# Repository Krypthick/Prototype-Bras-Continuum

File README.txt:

Base:

base_housing:
Le boîtier principal agit comme une base pour le bras. Il utilise des inserts chauffants filetés et des boulons M3.
Il contient :
	-circuit principal
	-circuit des pilotes pas à pas
	-circuit du système de gestion de batterie
	-les batteries
	-interrupteur
	-prise cylindrique DC

==============================
base_battery_retainer:
La pièce qui maintient les batteries en place.

==============================
base_motion_motor_housing:
Couvercle qui s'attache au boîtier avec des boulons M3 et tient les moteurs pas à pas.

==============================
base_fixed_segment:
Premier segment.

==============================
base_spacer_fixed_segment:
Espaceur entre (base_fixed_segment) et (base_motion_motor_housing), fixé avec des boulons M5. Fournit l'espace nécessaire pour les poulies attachées au réducteur.

============================================================
Gearbox:

gearbox_motor_gear:
Engrenage attaché et entraîné par le moteur pas à pas. Engrenage soleil.

==============================
gearbox_planet_gear:
Engrenage planète, aussi appelé satellite. Il y en a trois pour avoir un réducteur stable.

==============================
gearbox_ring_gear:
L'engrenage fixé au moteur pas à pas avec des boulons M3 a aussi comme fonction de contenir les pièces du réducteur.

==============================
gearbox_orbit:
La pièce qui relie les trois engrenages planètes et est attachée à l'arbre avec des boulons et écrous M4.

==============================
gearbox_shaft:
L'arbre attaché aux engrenages planètes et auquel on attache la poulie.

==============================
gearbox_shaft_attachment:
La poulie qui tient la corde permettant le mouvement du bras.

======================================================
Hand:

hand_segment:
Le dernier segment qui tient le support de la main avec des boulons et écrous M5 et tient la fin de la corde.

==============================

hand_motor_finger_mount:
Le support qui tient le petit moteur pas à pas avec des boulons M3 ainsi que les deux doigts de la pince avec des boulons M5.

==============================

hand_gripper:
Le doigt de la pince qui contient un roulement à billes 606z.

==============================

hand_bearing_M5_spacer:
La pièce qui relie le boulon M5 de diamètre 5 mm et le roulement à billes ayant un diamètre intérieur de 6 mm.

======================================================
Manette:

manette_housing:
Boîtier de la manette qui contient le circuit de la manette, la batterie 9V et le joystick. Il utilise des inserts chauffants filetés et des boulons M3.

==============================
manette_lid:
Le couvercle du boîtier de la manette attaché avec des boulons M3.

==============================
manette_pin:
La pièce qui permet d'utiliser les boutons de la manette plus facilement depuis l'extérieur.

======================================================
Segment:

La pièce principale qui guide la corde et donne la flexibilité nécessaire pour le mouvement du bras. Chaque segment a un boulon et un écrou M4, mais aussi une boule filetée de 10 mm de diamètre qui permet la rotation entre les différents segments.

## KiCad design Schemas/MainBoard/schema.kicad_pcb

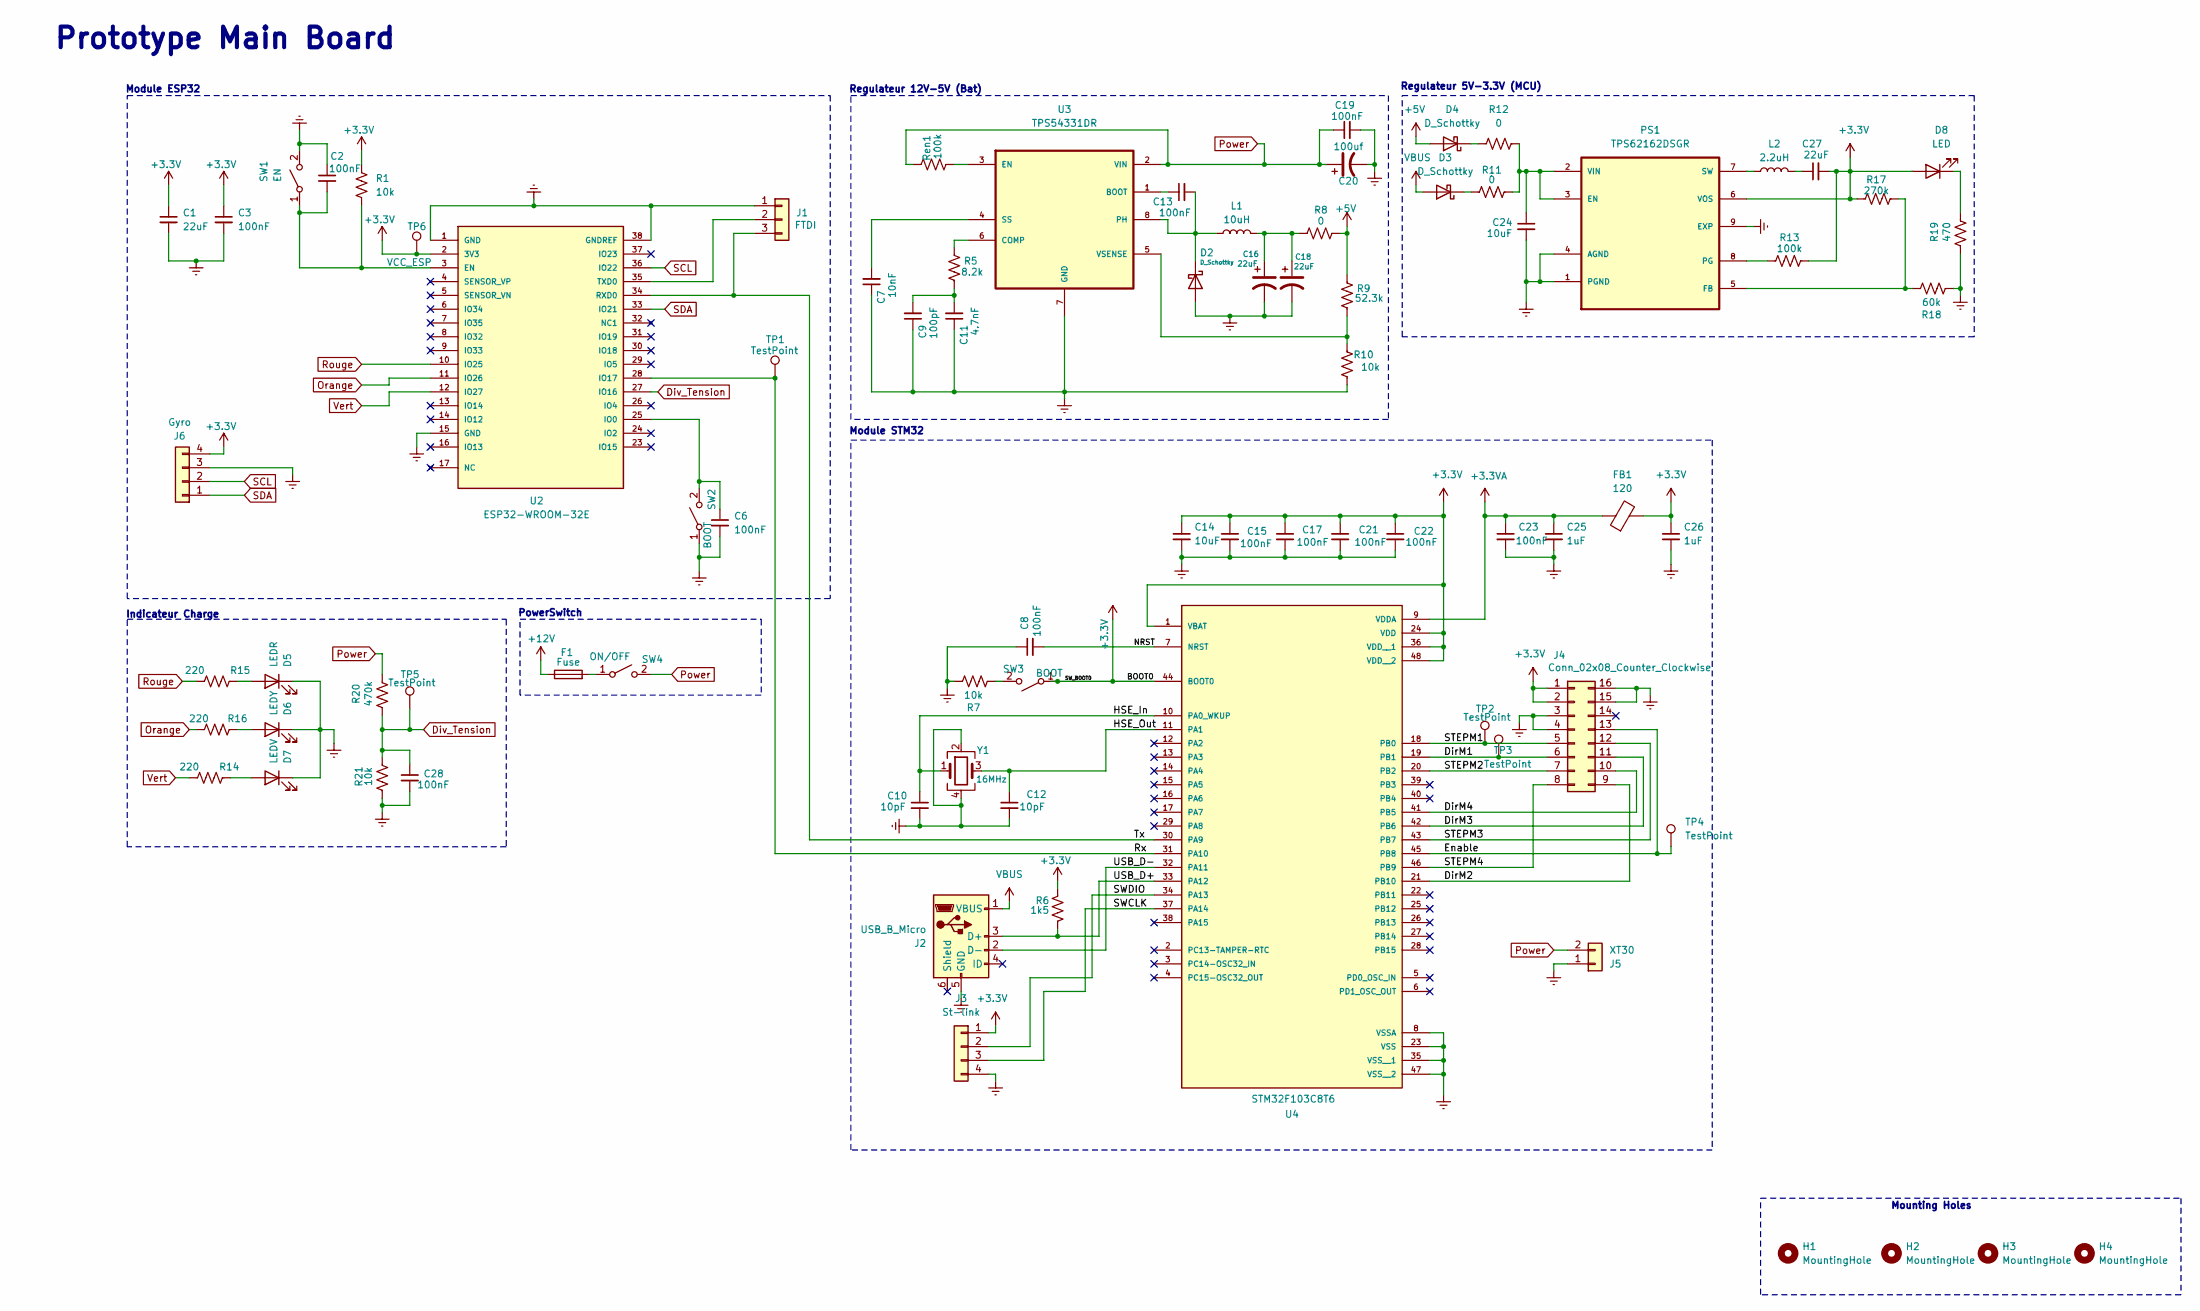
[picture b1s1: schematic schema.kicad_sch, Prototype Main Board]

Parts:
C1, C16, C18, C27: 22uF; C_0805_2012Metric_Pad1.18x1.45mm_HandSolder; MPN CL10A226MP8NUNE
C2, C3, C6, C8, C13, C15, C17, C19, C21, C22, C23: 100nF; C_0603_1608Metric_Pad1.08x0.95mm_HandSolder; MPN C0603C104K5RACTU
C7: 10nF; C_0603_1608Metric_Pad1.08x0.95mm_HandSolder; MPN CL10B103KB8NNNC
C9: 100pF; C_0603_1608Metric_Pad1.08x0.95mm_HandSolder; MPN CL10C101JB8NNNC
C10, C12: 10pF; C_0603_1608Metric_Pad1.08x0.95mm_HandSolder; MPN C0603C100J5GACTU
C11: 4.7nF; C_0603_1608Metric_Pad1.08x0.95mm_HandSolder; MPN CL10B473KB8NNNC
C14, C24: 10uF; C_0805_2012Metric_Pad1.18x1.45mm_HandSolder; MPN CL21B106KOQNNNE
C20: 100uf; CAP_YX_6P3X11_RUB; MPN 35ZLH100MEFC6.3X11
C25, C26: 1uF; C_0603_1608Metric_Pad1.08x0.95mm_HandSolder; MPN CL10B105KP8NNNC
C28: 100nF; C_0805_2012Metric_Pad1.18x1.45mm_HandSolder; MPN C0805C104K5RACTU
D2, D3, D4: D_Schottky; CDBC-G; MPN CDBC560-G
D5: LEDR; LED_0805_2012Metric_Pad1.15x1.40mm_HandSolder; MPN LTST-C171KRKT
D6: LEDY; LED_0805_2012Metric_Pad1.15x1.40mm_HandSolder; MPN LTST-C171KSKT
D7: LEDV; LED_0805_2012Metric_Pad1.15x1.40mm_HandSolder; MPN LTST-C171KGKT
D8: LED; LED_0805_2012Metric_Pad1.15x1.40mm_HandSolder; MPN LTST-C171KGKT
F1: Fuse; FUSC6125X279N; MPN 0679H9100-05
FB1: 120; L_0603_1608Metric_Pad1.05x0.95mm_HandSolder; MPN MI0603M121R-10
H1, H2, H3, H4: MountingHole; MountingHole_3.2mm_M3_DIN965_Pad
J1: FTDI; PinHeader_1x03_P2.54mm_Vertical
J2: USB_B_Micro; AMPHENOL_10118192-0001LF; MPN 10118192-0001LF
J3: St-link; PinHeader_1x04_P2.54mm_Vertical; MPN 61300411121
J4: Conn_02x08_Counter_Clockwise; CONN_7024616xx_MOL; MPN 0702461601
J5: XT30; AMASS_XT30U-M_1x02_P5.0mm_Vertical; MPN FIT0586
J6: Gyro; PinHeader_1x04_P2.54mm_Vertical; MPN 61300411121
L1: 10uH; IND_IHLP-4040DZ_VIS; MPN IHLP4040DZER100M01
L2: 2.2uH; INDC3225X170N; MPN BRL3225T2R2M
PS1: TPS62162DSGR; SON50P200X200X80-9N; PARTREV E
R1, R7, R10: 10k; R_0603_1608Metric_Pad0.98x0.95mm_HandSolder; MPN RC0603FR-0710KL
R5: 8.2k; R_0603_1608Metric_Pad0.98x0.95mm_HandSolder; MPN ERJ-3EKF8201V
R6: 1k5; R_0603_1608Metric_Pad0.98x0.95mm_HandSolder; MPN ERA-3AEB152V
R8, R11, R12: 0; RESC2012X50N; MPN CRCW08050000Z0EA
R9: 52.3k; R_0603_1608Metric_Pad0.98x0.95mm_HandSolder; MPN RC0603FR-0752K3L
R13: 100k; R_0603_1608Metric_Pad0.98x0.95mm_HandSolder; MPN RMCF0603FT100K
R14, R15, R16: 220; R_0603_1608Metric_Pad0.98x0.95mm_HandSolder; MPN CRGCQ0805F220R
R17: 270k; R_0603_1608Metric_Pad0.98x0.95mm_HandSolder; MPN RC0603FR-07270KL
R18: 60k; R_0603_1608Metric_Pad0.98x0.95mm_HandSolder; MPN RT0603BRD0760KL
R19: 470; R_0603_1608Metric_Pad0.98x0.95mm_HandSolder; MPN RC0603JR-07470RL
R20: 470k; R_0805_2012Metric_Pad1.20x1.40mm_HandSolder; MPN CRCW0805470KJNEA
R21: 10k; R_0805_2012Metric_Pad1.20x1.40mm_HandSolder; MPN RC0805JR-0710KL
Ren1: 100k; R_0603_1608Metric_Pad0.98x0.95mm_HandSolder; MPN RMCF0603FT100K
SW1: EN; SW_Tactile_SPST_NO_Straight_CK_PTS636Sx25SMTRLFS; MPN PTS636SK25FSMTR LFS
SW2, SW3: BOOT; SW_Tactile_SPST_NO_Straight_CK_PTS636Sx25SMTRLFS; MPN PTS636SK25FSMTR LFS
SW4: ON/OFF; TE_640456-2; MPN R1966ABLKBLKFF
TP1, TP2, TP3, TP4, TP5: TestPoint; TestPoint_Pad_1.5x1.5mm
TP6: VCC_ESP; TestPoint_Pad_1.5x1.5mm
U2: ESP32-WROOM-32E; XCVR_ESP32-WROOM-32E__16MB_; PARTREV 1.4
U3: TPS54331DR; SOIC127P599X175-8N; MPN TPS54331DR
U4: STM32F103C8T6; QFP50P900X900X160-48N; PARTREV 10
Y1: 16MHz; Crystal_SMD_2520-4Pin_2.5x2.0mm; MPN ABM8G-16.000MHZ-18-D2Y-T

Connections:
+3.3V: C1.1, C3.1, C14.1, C15.1, C17.1, C21.1, C22.1, C26.1, C27.2, D8.2 (A), FB1.2, J3.1, J4.1, J4.2, J6.4, PS1.6 (VOS), R1.1, R6.2, R13.2, R17.2, SW3.1 (A), TP6.1, U2.2 (3V3), U4.1 (VBAT), U4.24 (VDD), U4.36 (VDD__1), U4.44 (BOOT0), U4.48 (VDD__2)
+3.3VA: C23.1, C25.1, FB1.1, U4.9 (VDDA)
+5V: D4.2 (A), R8.2, R9.2
+12V: F1.1
/DirM1: J4.6, TP3.1, U4.19 (PB1)
/DirM2: J4.9, U4.21 (PB10)
/DirM3: J4.11, U4.42 (PB6)
/DirM4: J4.10, U4.41 (PB5)
/Enable: J4.13, TP4.1, U4.45 (PB8)
/HSE_In: C10.1, U4.10 (PA0_WKUP), Y1.1
/HSE_Out: C12.1, U4.11 (PA1), Y1.3
/NRST: C8.2, U4.7 (NRST)
/Rx: TP1.1, U2.28 (IO17), U4.31 (PA10)
/STEPM1: J4.5, TP2.1, U4.18 (PB0)
/STEPM2: J4.7, U4.20 (PB2)
/STEPM3: J4.12, U4.43 (PB7)
/STEPM4: J4.8, U4.46 (PB9)
/SWCLK: J3.3, U4.37 (PA14)
/SWDIO: J3.2, U4.34 (PA13)
/Tx: J1.3, U2.34 (RXD0), U4.30 (PA9)
/USB_D+: J2.3 (D+), R6.1, U4.33 (PA12)
/USB_D-: J2.2 (D-), U4.32 (PA11)
Div_Tension: C28.1, R20.1, R21.2, TP5.1, U2.27 (IO16)
unnamed: C9.2, C11.2, R5.1
unnamed: C16.1, C18.1, L1.2, R8.1
unnamed: C27.1, L2.2
unnamed: C13.2, D2.1 (K), L1.1, U3.8 (PH)
unnamed: D3.1 (K), R11.1
unnamed: D4.1 (K), R12.1
unnamed: D5.2 (A), R15.1
unnamed: D6.2 (A), R16.1
unnamed: D7.2 (A), R14.1
unnamed: D8.1 (K), R19.2
unnamed: J1.2, U2.35 (TXD0)
unnamed: C24.1, PS1.2 (VIN), PS1.3 (EN), R11.2, R12.2
unnamed: PS1.5 (FB), R17.1, R18.2
unnamed: PS1.8 (PG), R13.1
unnamed: L2.1, PS1.7 (SW)
unnamed: C2.2, R1.2, SW1.1 (A), U2.3 (EN)
unnamed: C6.1, SW2.2 (B), U2.25 (IO0)
unnamed: R7.1, SW3.2 (B)
unnamed: F1.2, SW4.1 (A)
unnamed: C13.1, U3.1 (BOOT)
unnamed: R5.2, U3.6 (COMP)
unnamed: Ren1.1, U3.3 (EN)
unnamed: C7.2, U3.4 (SS)
unnamed: R9.1, R10.2, U3.5 (VSENSE)
Orange: R16.2, U2.11 (IO26)
Power: C19.1, C20.1, J5.2, R20.2, Ren1.2, SW4.2 (B), U3.2 (VIN)
Rouge: R15.2, U2.10 (IO25)
SCL: J6.2, U2.36 (IO22)
SDA: J6.1, U2.33 (IO21)
VBUS: D3.2 (A), J2.1 (VBUS)
Vert: R14.2, U2.12 (IO27)

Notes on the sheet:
Indicateur Charge
PowerSwitch
Module ESP32
Regulateur 5V-3.3V (MCU)
Mounting Holes
Module STM32
Regulateur 12V-5V (Bat)
Prototype Main Board

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
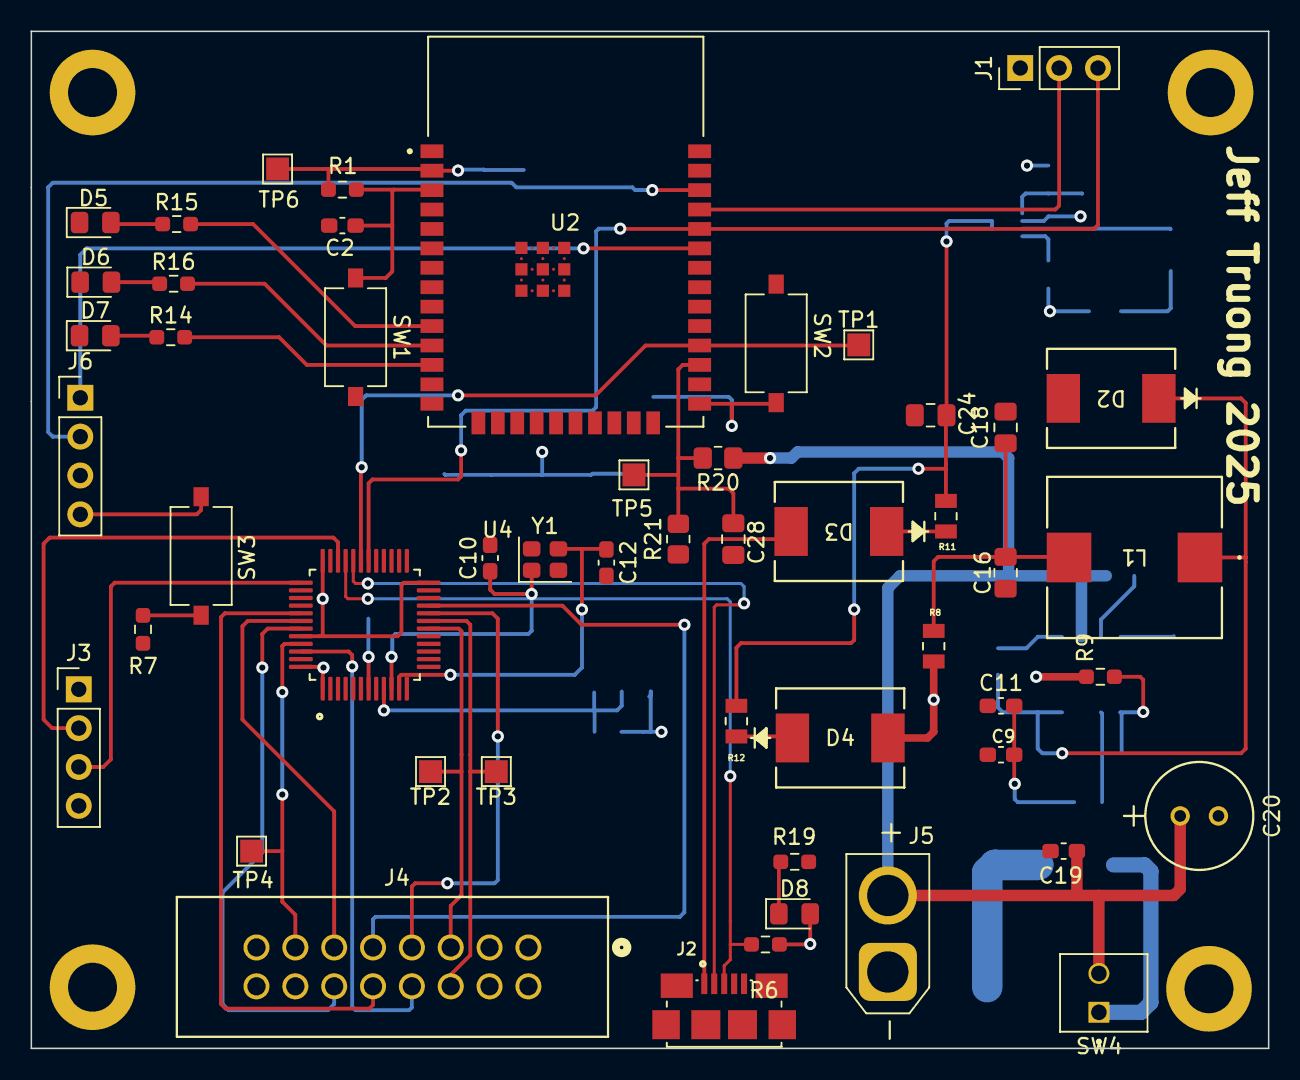
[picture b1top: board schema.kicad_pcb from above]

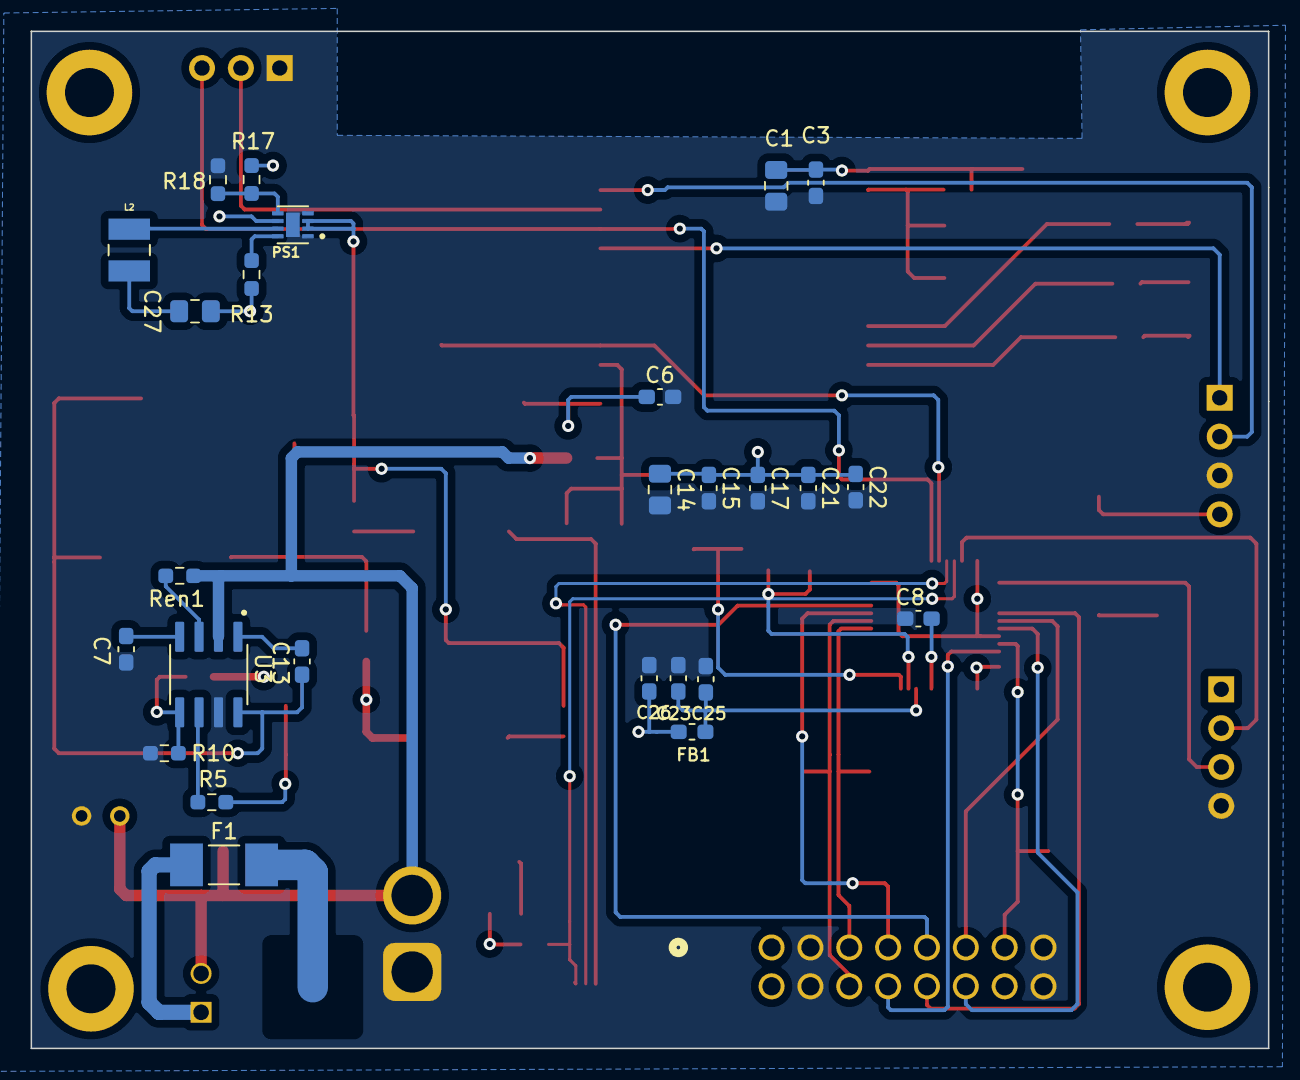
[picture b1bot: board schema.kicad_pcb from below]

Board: 4 copper layers, 80.9 x 66.5 mm, 81 parts (26 on the bottom side), 54 nets.

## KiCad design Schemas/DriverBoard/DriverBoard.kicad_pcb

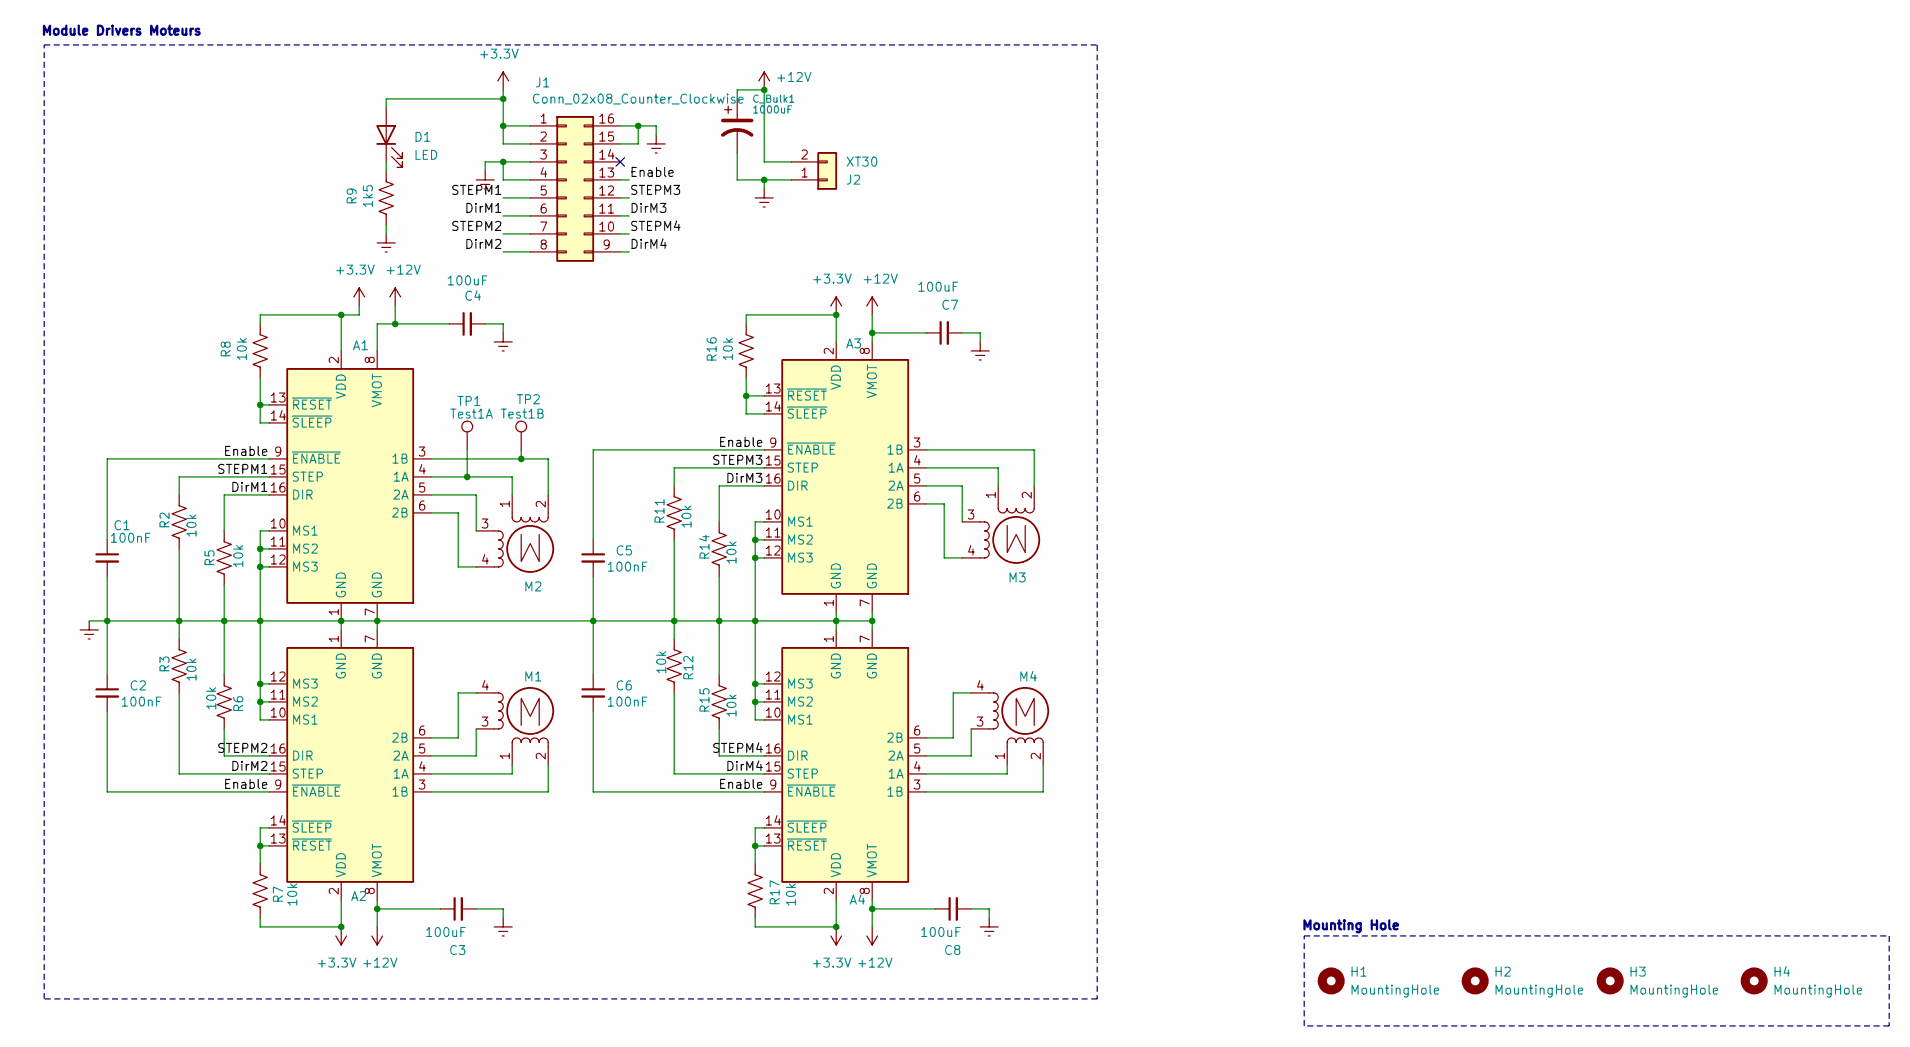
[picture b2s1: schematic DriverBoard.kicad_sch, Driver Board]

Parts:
A1, A2, A3, A4: Pololu_Breakout_A4988; MODULE_A4988_STEPPER_MOTOR_DRIVER_CARRIER
C1, C2, C5, C6: 100nF; C_0603_1608Metric_Pad1.08x0.95mm_HandSolder; MPN C0603C104K5RACTU
C3, C4, C7, C8: 100uF; WCAP-ASLI_6.3X5.5_DXL_; MPN 865080343009
C_Bulk1: 1000uF; CHEMI-JB5; MPN APSG160ELL102MJB5S
D1: LED; LED_0603_1608Metric_Pad1.05x0.95mm_HandSolder; MPN LTST-C171KGKT
H1, H2, H3, H4: MountingHole; MountingHole_3.2mm_M3_DIN965_Pad
J1: Conn_02x08_Counter_Clockwise; CONN_7024616xx_MOL; MPN 0702461601
J2: XT30; AMASS_XT30U-F_1x02_P5.0mm_Vertical; MPN FIT0586
M1, M2, M3, M4: Stepper_Motor_bipolar; CONN_SDA-41791_M450_04_MOL; MPN 0026604040
R2, R3, R5, R6, R7, R8, R11, R12, R14, R15, R16, R17: 10k; R_0603_1608Metric_Pad0.98x0.95mm_HandSolder; MPN RC0603FR-0710KL
R9: 1k5; R_0603_1608Metric_Pad0.98x0.95mm_HandSolder; MPN ERA-3AEB152V
TP1: Test1A; TestPoint_Pad_2.5x2.5mm
TP2: Test1B; TestPoint_Pad_2.5x2.5mm

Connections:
+3.3V: A1.2 (VDD), A2.2 (VDD), A3.2 (VDD), A4.2 (VDD), D1.2 (A), J1.1, J1.2, R7.2, R8.2, R16.2, R17.1
+12V: A1.8 (VMOT), A2.8 (VMOT), A3.8 (VMOT), A4.8 (VMOT), C3.1, C4.1, C7.1, C8.1, C_Bulk1.1, J2.2
/DirM1: A1.16 (DIR), J1.6, R5.2
/DirM2: A2.15 (STEP), J1.8, R3.2
/DirM3: A3.16 (DIR), J1.11, R14.1
/DirM4: A4.15 (STEP), J1.9, R12.1
/Enable: A1.9 (~ENABLE), A2.9 (~ENABLE), A3.9 (~ENABLE), A4.9 (~ENABLE), C1.1, C2.2, C5.1, C6.2, J1.13
/STEPM1: A1.15 (STEP), J1.5, R2.1
/STEPM2: A2.16 (DIR), J1.7, R6.1
/STEPM3: A3.15 (STEP), J1.12, R11.1
/STEPM4: A4.16 (DIR), J1.10, R15.2
GNDREF: A1.1 (GND), A1.7 (GND), A1.10 (MS1), A1.11 (MS2), A1.12 (MS3), A2.1 (GND), A2.7 (GND), A2.10 (MS1), A2.11 (MS2), A2.12 (MS3), A3.1 (GND), A3.7 (GND), A3.10 (MS1), A3.11 (MS2), A3.12 (MS3), A4.1 (GND), A4.7 (GND), A4.10 (MS1), A4.11 (MS2), A4.12 (MS3), C1.2, C2.1, C3.2, C4.2, C5.2, C6.1, C7.2, C8.2, C_Bulk1.2, J1.3, J1.4, J1.15, J1.16, J2.1, R2.2, R3.1, R5.1, R6.2, R9.1, R11.2, R12.2, R14.2, R15.1
unnamed: A1.4 (1A), M2.1, TP1.1
unnamed: A1.3 (1B), M2.2 (-), TP2.1
unnamed: A1.5 (2A), M2.3
unnamed: A1.6 (2B), M2.4
unnamed: A1.13 (~RESET), A1.14 (~SLEEP), R8.1
unnamed: A2.4 (1A), M1.1
unnamed: A2.3 (1B), M1.2 (-)
unnamed: A2.5 (2A), M1.3
unnamed: A2.6 (2B), M1.4
unnamed: A2.13 (~RESET), A2.14 (~SLEEP), R7.1
unnamed: A3.4 (1A), M3.1
unnamed: A3.3 (1B), M3.2 (-)
unnamed: A3.5 (2A), M3.3
unnamed: A3.6 (2B), M3.4
unnamed: A3.13 (~RESET), A3.14 (~SLEEP), R16.1
unnamed: A4.4 (1A), M4.1
unnamed: A4.3 (1B), M4.2 (-)
unnamed: A4.5 (2A), M4.3
unnamed: A4.6 (2B), M4.4
unnamed: A4.13 (~RESET), A4.14 (~SLEEP), R17.2
unnamed: D1.1 (K), R9.2

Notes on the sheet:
Mounting Hole
Module Drivers Moteurs

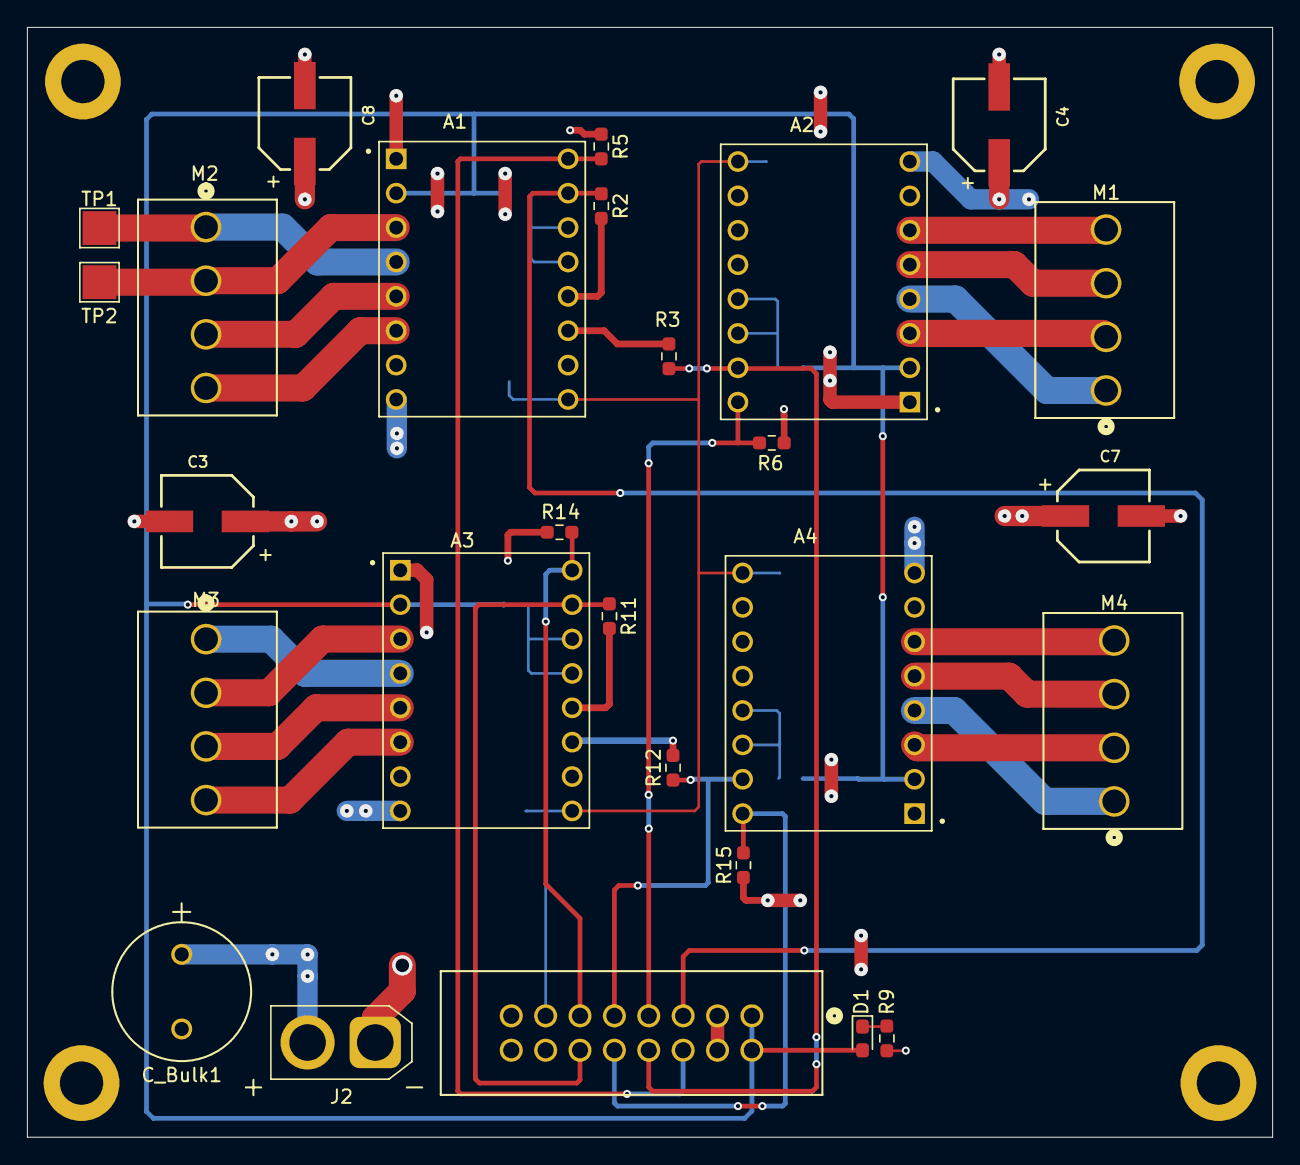
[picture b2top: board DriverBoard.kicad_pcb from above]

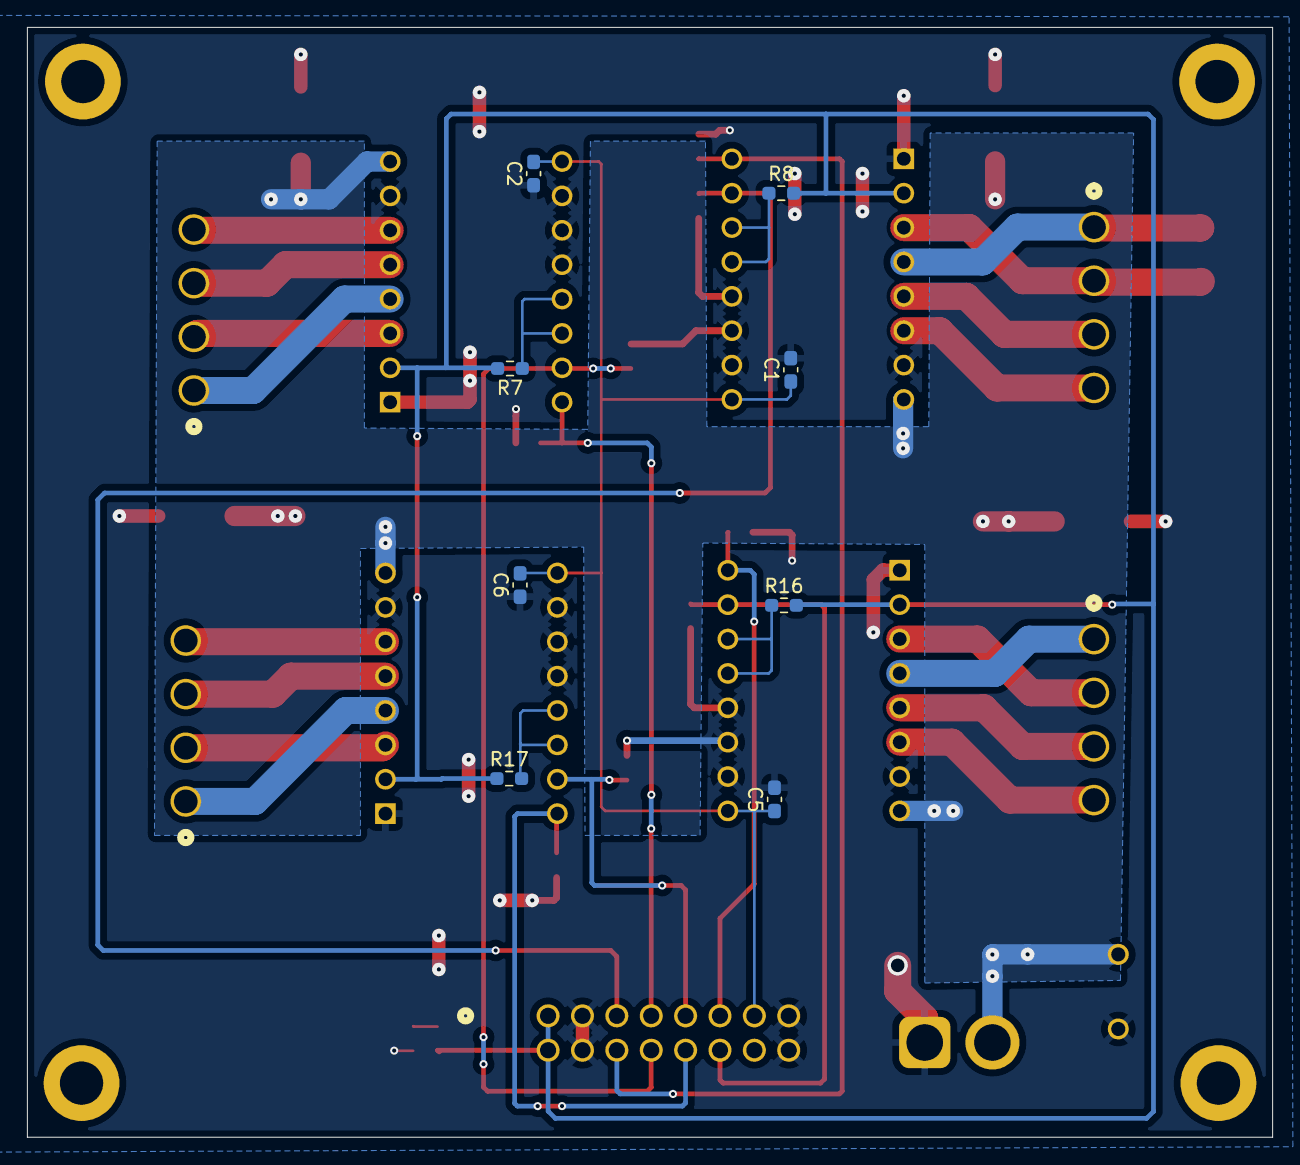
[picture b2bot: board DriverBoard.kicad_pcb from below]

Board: 2 copper layers, 92.0 x 82.0 mm, 39 parts (8 on the bottom side), 33 nets.

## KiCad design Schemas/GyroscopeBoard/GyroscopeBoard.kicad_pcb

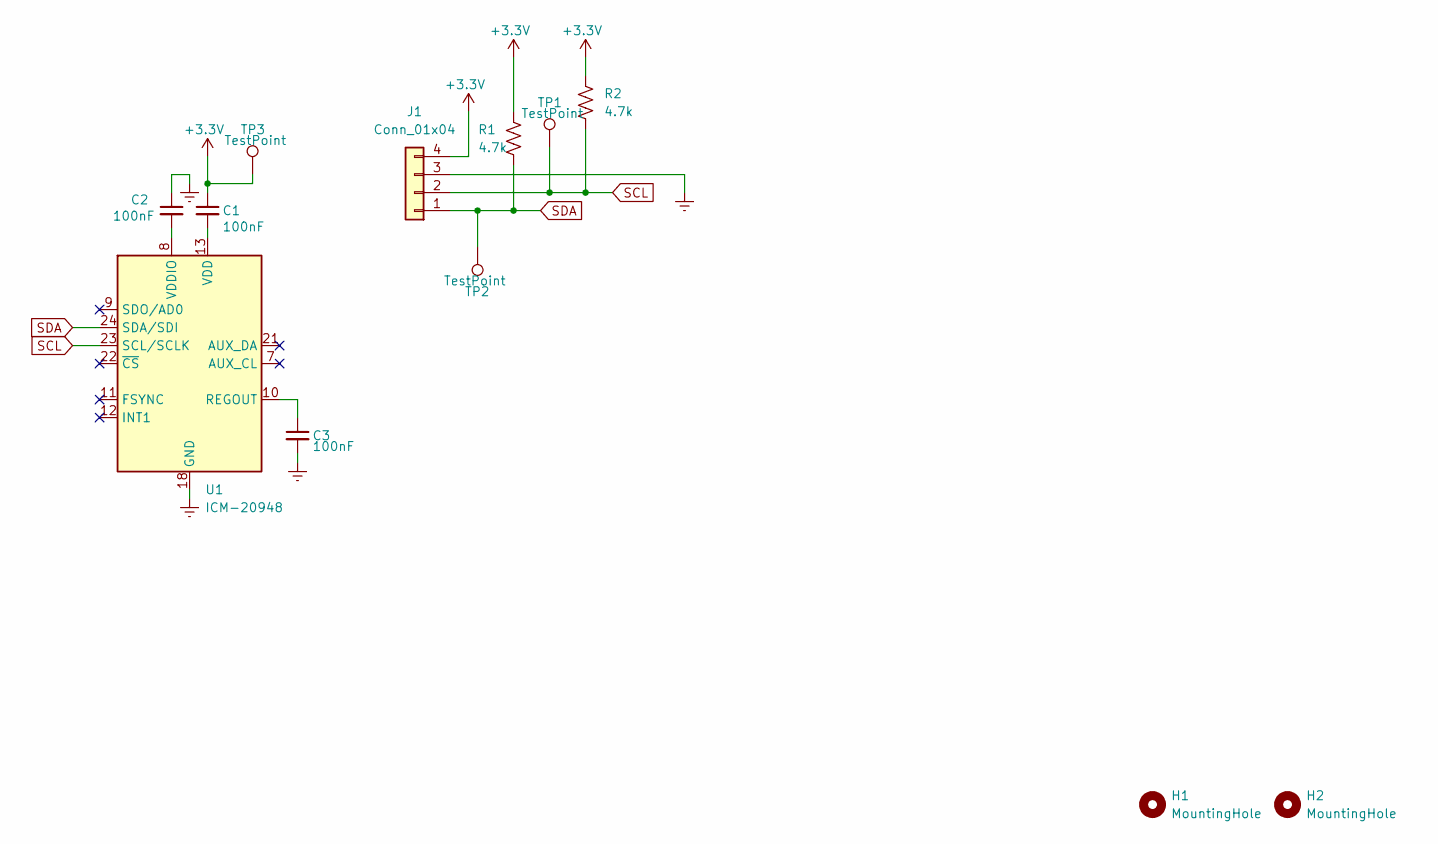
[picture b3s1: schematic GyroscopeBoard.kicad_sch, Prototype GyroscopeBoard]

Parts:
C1, C2, C3: 100nF; C_0805_2012Metric_Pad1.18x1.45mm_HandSolder; MPN C0603C104K5RACTU
H1, H2: MountingHole; MountingHole_3.2mm_M3_DIN965_Pad
J1: Conn_01x04; CONN_A-6373-04A_MOL
R1, R2: 4.7k; R_0805_2012Metric_Pad1.20x1.40mm_HandSolder; MPN RC0603FR-0710KL
TP1, TP2, TP3: TestPoint; TestPoint_Pad_1.0x1.0mm
U1: ICM-20948; InvenSense_QFN-24_3x3mm_P0.4mm

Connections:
+3.3V: C1.1, J1.4, R1.1, R2.1, TP3.1
GNDREF: C2.1, C3.2, J1.3, U1.18 (GND), U1.20 (GND)
unnamed: C3.1, U1.10 (REGOUT)
unnamed: C1.2, U1.13 (VDD)
unnamed: C2.2, U1.8 (VDDIO)
SCL: J1.2, R2.2, TP1.1, U1.23 (SCL/SCLK)
SDA: J1.1, R1.2, TP2.1, U1.24 (SDA/SDI)

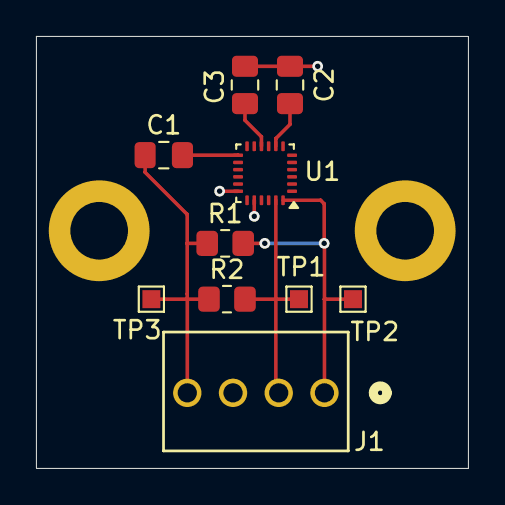
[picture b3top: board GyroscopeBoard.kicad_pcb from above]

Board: 2 copper layers, 24.0 x 24.0 mm, 12 parts (0 on the bottom side), 7 nets.

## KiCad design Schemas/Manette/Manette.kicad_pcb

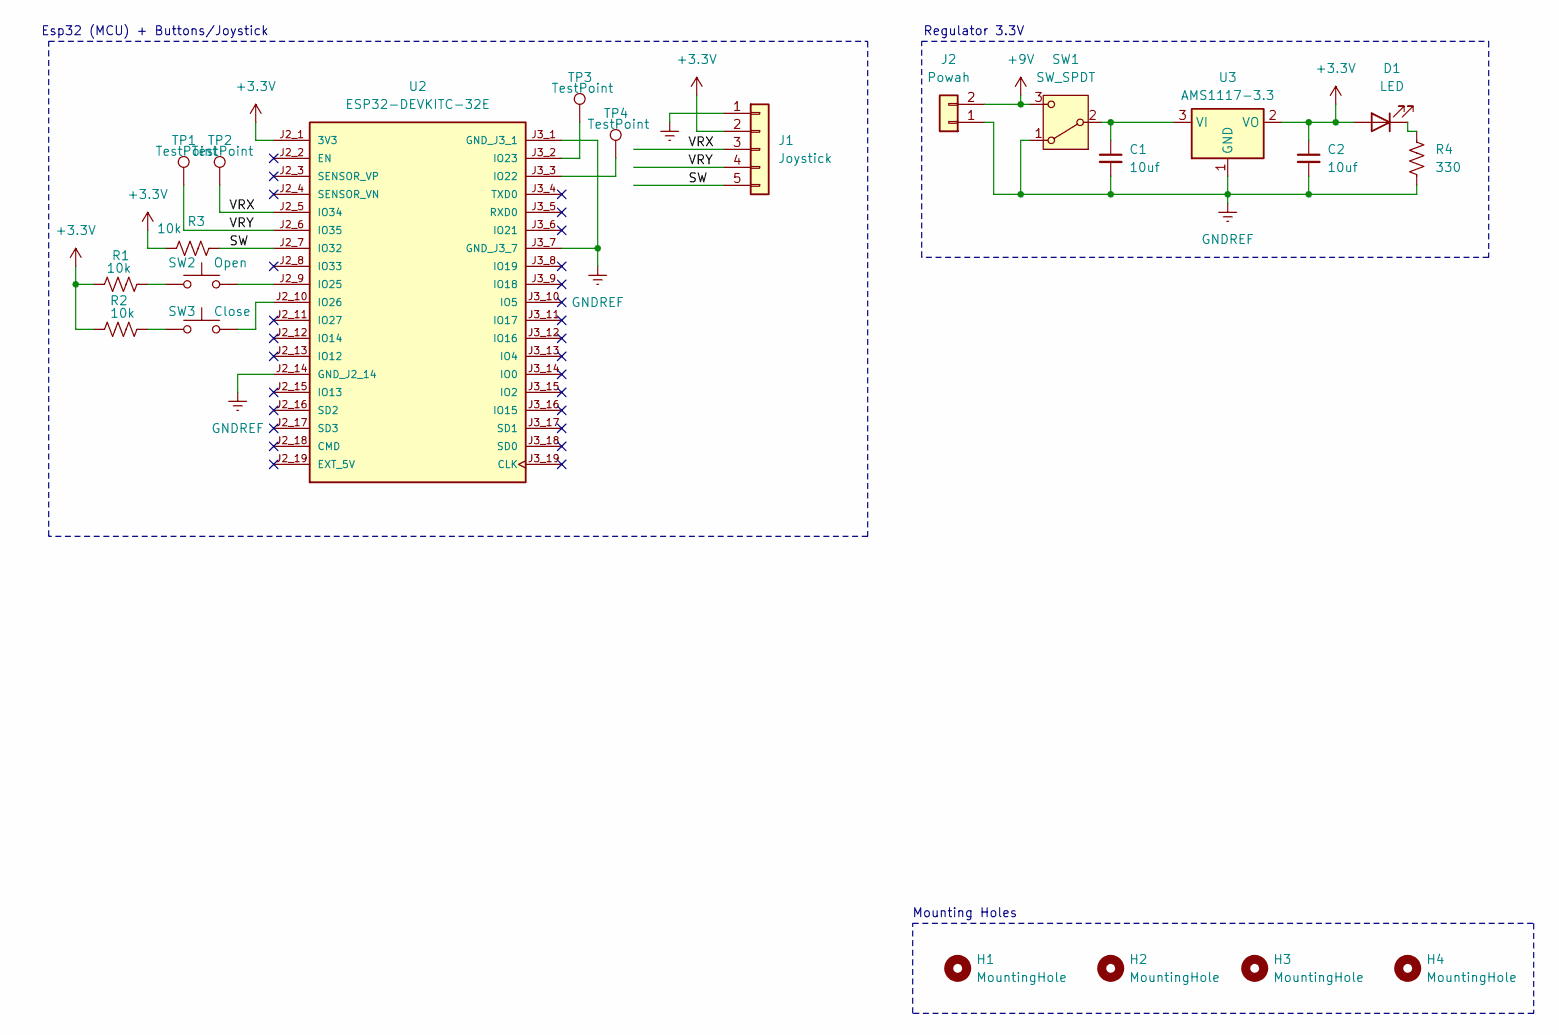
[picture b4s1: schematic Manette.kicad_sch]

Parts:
C1, C2: 10uf; C_0805_2012Metric_Pad1.18x1.45mm_HandSolder; MPN CL21B106KOQNNNE
D1: LED; LED_0805_2012Metric; MPN LTST-C171KGKT
H1, H2, H3, H4: MountingHole; MountingHole_3.2mm_M3_DIN965
J1: Joystick; PinHeader_1x05_P2.54mm_Vertical; MPN PH1RB-05-UA
J2: Powah; TE_640456-2; MPN 640456-2
R1, R2, R3: 10k; R_0805_2012Metric_Pad1.20x1.40mm_HandSolder; MPN RC0805JR-0710KL
R4: 330; R_0805_2012Metric_Pad1.20x1.40mm_HandSolder; MPN RMCF0805JT330R
SW1: SW_SPDT; SW_JS102011SAQN; MPN JS102011SAQN
SW2: Open; SW_Tactile_SPST_NO_Straight_CK_PTS636Sx25SMTRLFS; MPN PTS636SK25FSMTR LFS
SW3: Close; SW_Tactile_SPST_NO_Straight_CK_PTS636Sx25SMTRLFS; MPN PTS636SK25FSMTR LFS
TP1, TP2, TP3, TP4: TestPoint; TestPoint_Pad_1.5x1.5mm
U2: ESP32-DEVKITC-32E; MODULE_ESP32-DEVKITC-32E; PARTREV 1.4
U3: AMS1117-3.3; SOT-223-3_TabPin2; MPN AMS1117-3.3

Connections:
+3.3V: C2.1, D1.2 (A), J1.2, R1.1, R2.1, R3.1, U2.J2_1 (3V3), U3.2 (VO)
+9V: J2.2, SW1.3 (C)
/SW: J1.5, R3.2, U2.J2_7 (IO32)
/VRX: J1.3, TP2.1, U2.J2_5 (IO34)
/VRY: J1.4, TP1.1, U2.J2_6 (IO35)
GNDREF: C1.2, C2.2, J1.1, J2.1, R4.1, SW1.1 (A), U2.J2_14 (GND_J2_14), U2.J3_1 (GND_J3_1), U2.J3_7 (GND_J3_7), U3.1 (GND)
unnamed: D1.1 (K), R4.2
unnamed: R1.2, SW2.1
unnamed: R2.2, SW3.1
unnamed: C1.1, SW1.2 (B), U3.3 (VI)
unnamed: TP4.1, U2.J3_3 (IO22)
unnamed: TP3.1, U2.J3_2 (IO23)
unnamed: SW2.2, U2.J2_9 (IO25)
unnamed: SW3.2, U2.J2_10 (IO26)

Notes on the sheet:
Regulator 3.3V
Mounting Holes
Esp32 (MCU) + Buttons/Joystick

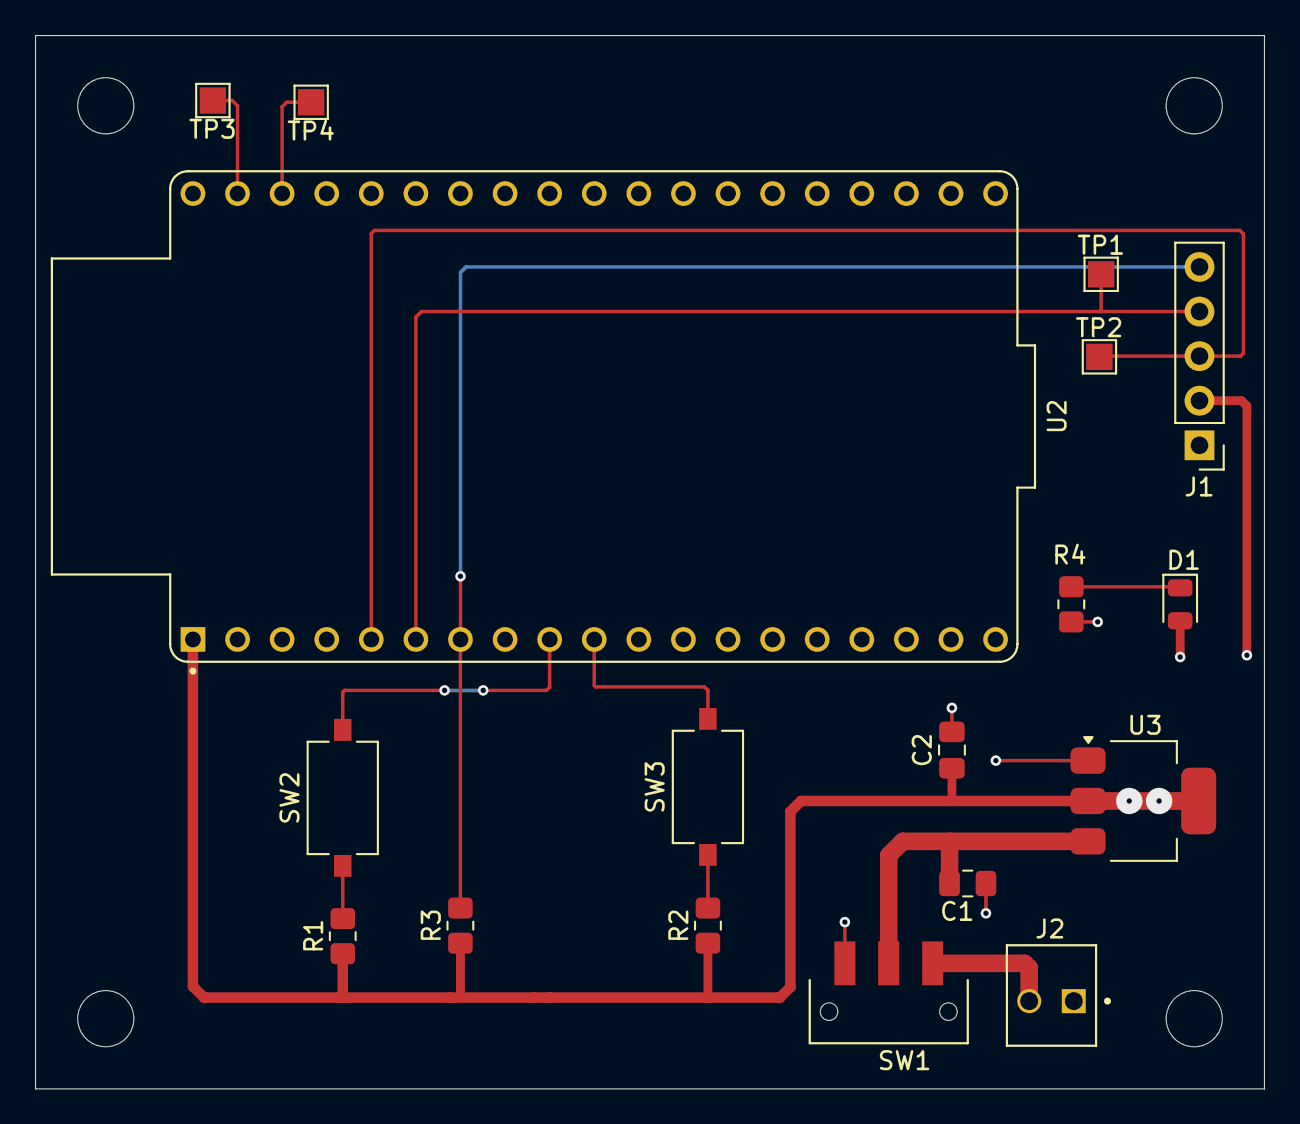
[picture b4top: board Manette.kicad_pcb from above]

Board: 2 copper layers, 70.0 x 60.0 mm, 22 parts (0 on the bottom side), 14 nets.

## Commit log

2026-05-25 models ajouter
2026-05-29 ajout de commentaire
